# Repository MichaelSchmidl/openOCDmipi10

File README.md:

# openOCDmipi10
Adaptor PCB for openOCD debugger to MIPI-10 socket

To be able to use OLIMEX MIPI-10 cables to connect ICprog OpenOCD adaptors to hardware
providing a MIPI-10 connector, the small PCB can be used.
<p>
PCBs can be ordered directly from OSH PARK https://oshpark.com/shared_projects/XA7GePBO
<p>
Assembly of PCB is easy. For the 10-pin header, cut a longer strip of sockets to 2x5 and
assemble the PCB between the pins.<p>
The MIPI-10 header is of type FTSH-105-XX-X-DV.
<p>

<p>

<p>

<p>

<p>

<p>

<p>

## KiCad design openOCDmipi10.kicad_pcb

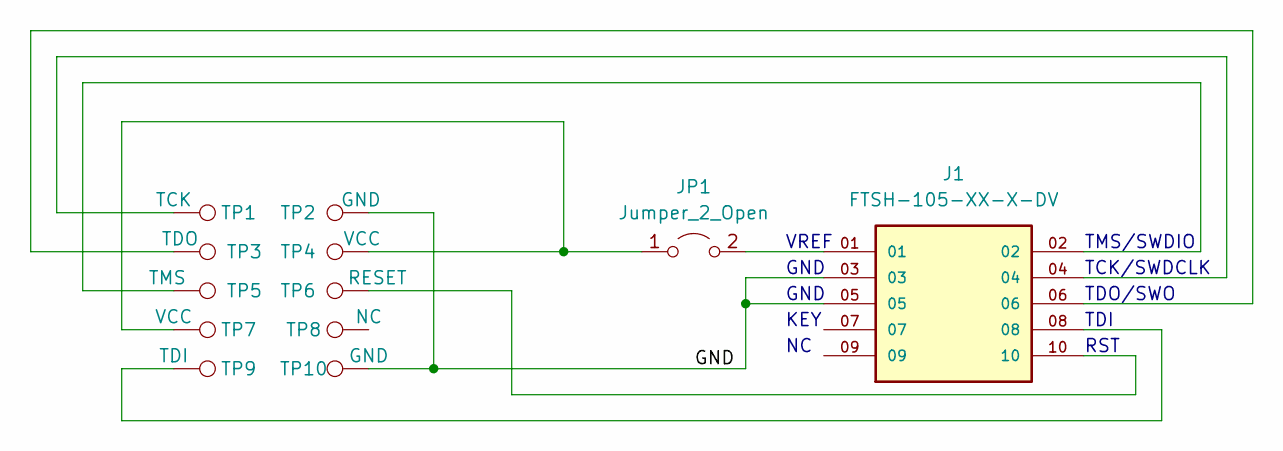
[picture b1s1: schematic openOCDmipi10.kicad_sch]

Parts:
J1: FTSH-105-XX-X-DV; SAMTEC_FTSH-105-XX-X-DV; PARTREV H
JP1: Jumper_2_Open; TestPoint_2Pads_Pitch2.54mm_Drill0.8mm
TP1: TCK; TestPoint_Pad_1.5x1.5mm
TP2, TP10: GND; TestPoint_Pad_1.5x1.5mm
TP3: TDO; TestPoint_Pad_1.5x1.5mm
TP4, TP7: VCC; TestPoint_Pad_1.5x1.5mm
TP5: TMS; TestPoint_Pad_1.5x1.5mm
TP6: RESET; TestPoint_Pad_1.5x1.5mm
TP8: NC; TestPoint_Pad_1.5x1.5mm
TP9: TDI; TestPoint_Pad_1.5x1.5mm

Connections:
/GND: J1.03, J1.05, TP2.1, TP10.1
unnamed: J1.01, JP1.2 (B)
unnamed: J1.04, TP1.1
unnamed: J1.06, TP3.1
unnamed: J1.02, TP5.1
unnamed: J1.10, TP6.1
unnamed: JP1.1 (A), TP4.1, TP7.1
unnamed: J1.08, TP9.1

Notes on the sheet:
GND
TDO/SWO
TDI
TCK/SWDCLK
RST
TMS/SWDIO
VREF
KEY

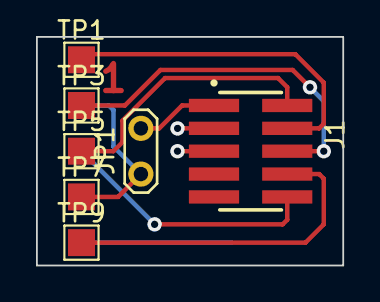
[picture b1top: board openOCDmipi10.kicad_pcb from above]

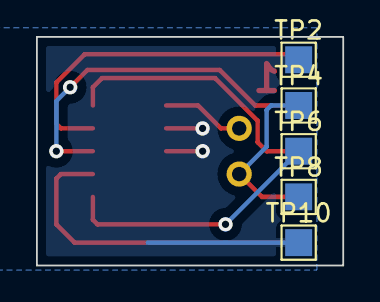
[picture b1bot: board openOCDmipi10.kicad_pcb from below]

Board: 2 copper layers, 17.0 x 12.7 mm, 12 parts (5 on the bottom side), 8 nets.

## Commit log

2022-03-27 added KiCAD files, GERBER Files and pictures
2023-03-30 Add files via upload
    added schematic
